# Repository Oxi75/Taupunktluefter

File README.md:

Dies ist meine erweiterte Version vom Taupunktlüfter mit Logging-Funktion der Maker Media GmbH.
Das Original mit den wichtigsten Fragen rund um den Taupunktlüfter beantwortet eine **[FAQ](https://heise.de/-6526328)**. Die vollständigen Artikel zum Projekt gibt es in der **[Make-Ausgabe 1/22 ab Seite 22](https://www.heise.de/select/make/2022/1/2135511212557842576)** und in der **[Make-Ausgabe 2/22 ab Seite 82](https://www.heise.de/select/make/2022/2/2204711461516715363)** zu lesen.

Das Original Github Projekt liegt hier: https://github.com/MakeMagazinDE/Taupunktluefter

# Taupunktlüfter mit Datenlogger V3.1

Sensorspannungsversorgung nicht mehr direkt über +5V sondern über Digital Out 8
des Arduinos angebunden. Hintergrund: Starke Störungen auf den Sensorleitungen,
konnte System in eine Endlos-Reboot-Schleife schicken (permanenter
Sensorfehler). Ende der Schleife erst durch hartes Abschalten der
(Sensor)Spannungsversorgung.

# Taupunktlüfter mit Datenlogger V3.0

* Unterstützung von bis zu vier Tür-Sensoren. D.h. wenn der entsprechende Sensor
anzeigt, dass die Tür nicht geschlossen ist, springt auch der Lüfter nicht an.
Als Sensoren können einfache Schließer (z.B. Magnetschalter) zum Einsatz kommen.
Schalter geschlossen, bedeutet Tür geschlossen.
Auf dem PCB sind Jumper vorgesehen um die Schalter zu überbrücken.
Wird eine offene Tür erkannt, so geht einerseits die Hinweis-LED permanent an,
andererseits wird eine entsprechende Information auf dem Display ausgegeben.
* Display-Auto-Off
Das Backlight des Displays wird nach einer bestimmten Zeit deaktiviert. Um es wieder zu
aktivieren, ist ein dafür vorgesehener Taster zu drücken.
* Umbenennung der Sensoren
„Sensor 1“ und „Sensor 2“ wurden umbenannt nach „Sensor I“ für „Sensor innen“ und
„Sensor A“ für „Sensor außen“.
* Erstellung von Schaltplan und Layout in KiCad 6.0;
Platine passend für Gehäuse Maße: 200 x 120 x 57 mm Deckel klar
https://www.ebay.de/itm/312566082994?var=611287841843

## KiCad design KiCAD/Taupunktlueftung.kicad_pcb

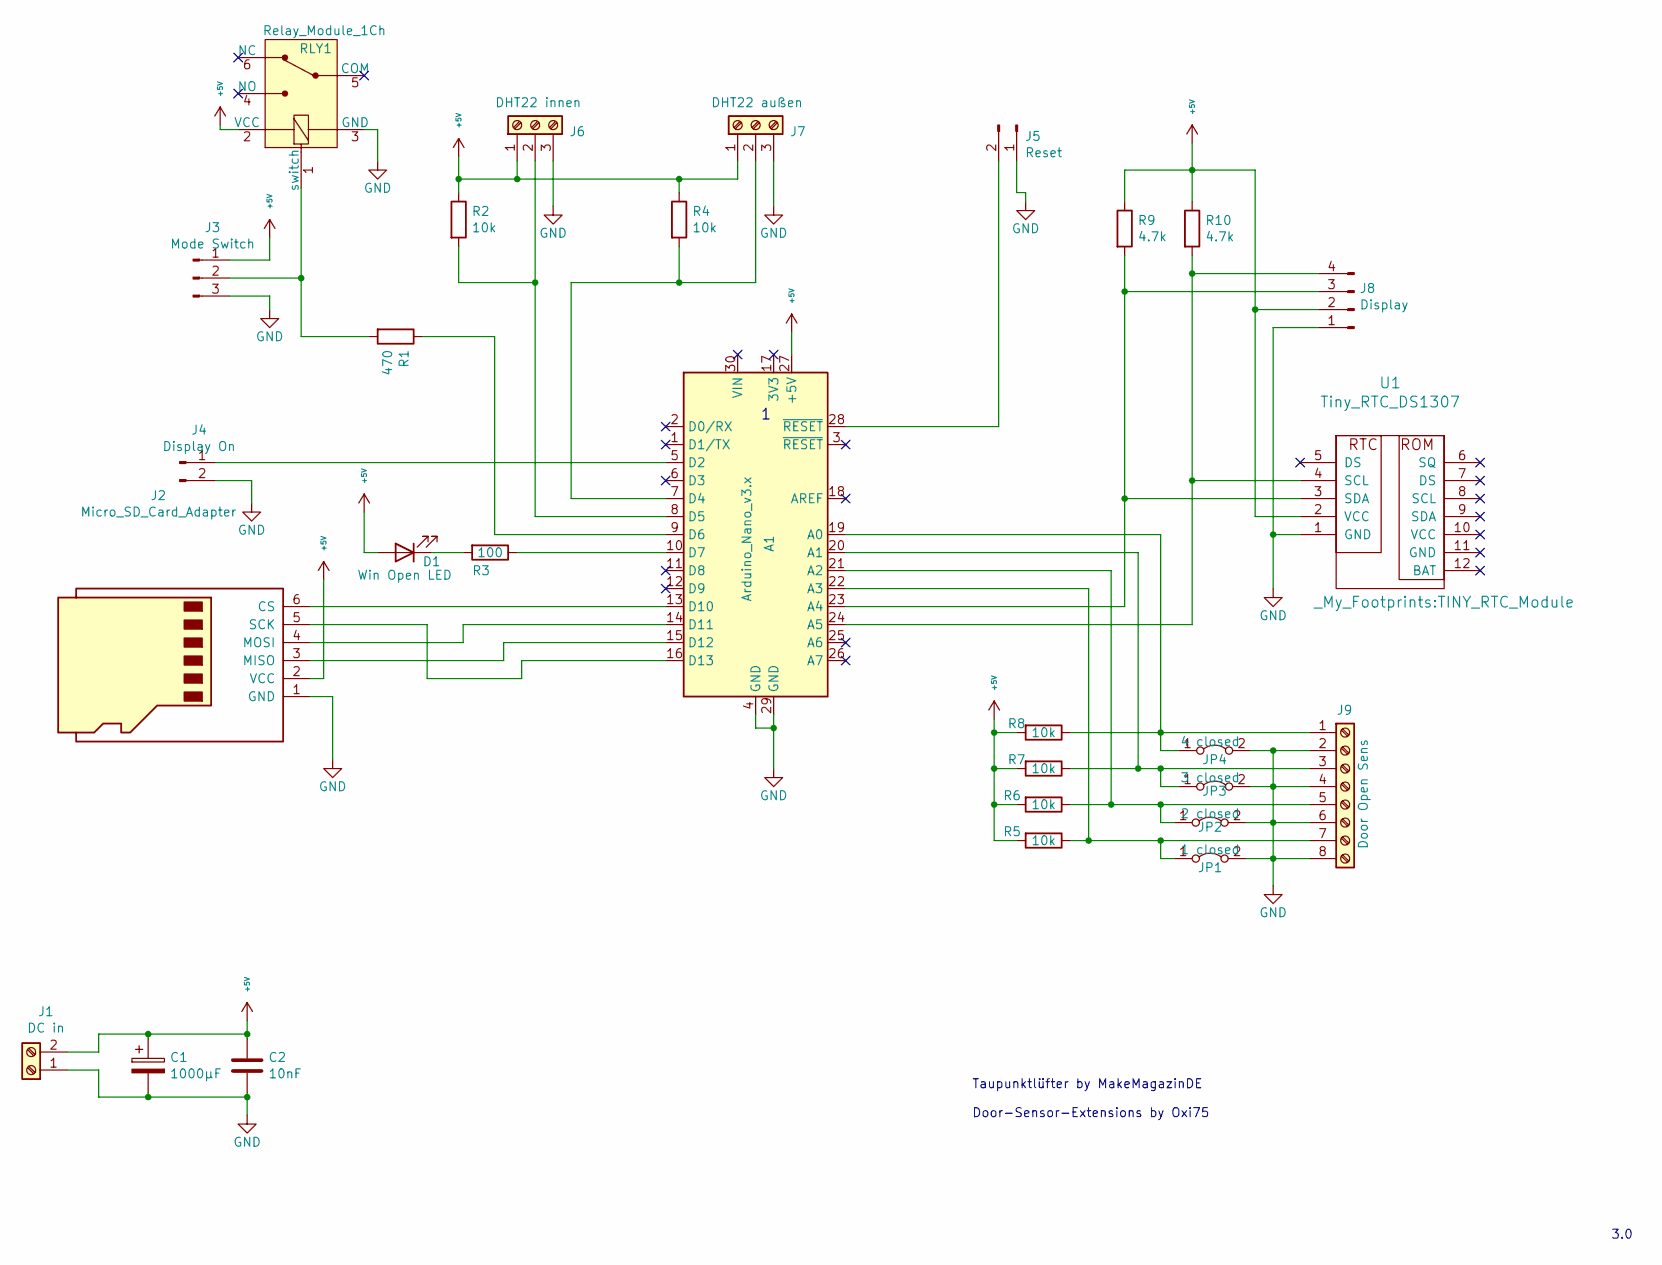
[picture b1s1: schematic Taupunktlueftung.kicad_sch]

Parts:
A1: Arduino_Nano_v3.x; Arduino_Nano
C1: 1000µF; CP_Radial_D8.0mm_P5.00mm
C2: 10nF; C_Rect_L9.0mm_W2.5mm_P7.50mm_MKT
D1: Win Open LED; LED_D5.0mm
J1: DC in; TerminalBlock_RND_205-00012_1x02_P5.00mm_Horizontal
J2: Micro_SD_Card_Adapter; MicroSD-Module_upright
J3: Mode Switch; PinHeader_1x03_P2.54mm_Vertical
J4: Display On; PinHeader_1x02_P2.54mm_Vertical
J5: Reset; PinHeader_1x02_P2.54mm_Vertical
J6: DHT22 innen; TerminalBlock_RND_205-00013_1x03_P5.00mm_Horizontal
J7: DHT22 außen; TerminalBlock_RND_205-00013_1x03_P5.00mm_Horizontal
J8: Display; PinHeader_1x04_P2.54mm_Vertical
J9: Door Open Sens; TerminalBlock_RND_205-00018_1x08_P5.00mm_Horizontal
JP1: 1 closed; PinHeader_1x02_P2.54mm_Vertical
JP2: 2 closed; PinHeader_1x02_P2.54mm_Vertical
JP3: 3 closed; PinHeader_1x02_P2.54mm_Vertical
JP4: 4 closed; PinHeader_1x02_P2.54mm_Vertical
R1: 470; R_Axial_DIN0309_L9.0mm_D3.2mm_P12.70mm_Horizontal
R2, R4, R5, R6, R7, R8: 10k; R_Axial_DIN0309_L9.0mm_D3.2mm_P12.70mm_Horizontal
R3: 100; R_Axial_DIN0309_L9.0mm_D3.2mm_P12.70mm_Horizontal
R9, R10: 4.7k; R_Axial_DIN0309_L9.0mm_D3.2mm_P12.70mm_Horizontal
RLY1: Relay_Module_1Ch
U1: Tiny_RTC_DS1307; TINY_RTC_Module

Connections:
+5V: A1.27 (+5V), C1.1, C2.1, D1.2 (A), J1.2, J2.2 (VCC), J3.1, J6.1, J7.1, J8.2, R2.1, R4.1, R5.2, R6.2, R7.2, R8.2, R9.1, R10.1, RLY1.2 (VCC), U1.2 (VCC)
GND: A1.4 (GND), A1.29 (GND), C1.2, C2.2, J1.1, J2.1 (GND), J3.3, J4.2, J5.1, J6.3, J7.3, J8.1, J9.2, J9.4, J9.6, J9.8, JP1.2 (B), JP2.2 (B), JP3.2 (B), JP4.2 (B), RLY1.3 (GND), U1.1 (GND)
unnamed: A1.5 (D2), J4.1
unnamed: A1.7 (D4), J7.2, R4.2
unnamed: A1.8 (D5), J6.2, R2.2
unnamed: A1.9 (D6), R1.1
unnamed: A1.10 (D7), R3.1
unnamed: A1.13 (D10), J2.6 (CS)
unnamed: A1.14 (D11), J2.4 (MOSI)
unnamed: A1.15 (D12), J2.3 (MISO)
unnamed: A1.16 (D13), J2.5 (SCK)
unnamed: A1.19 (A0), J9.1, JP4.1 (A), R8.1
unnamed: A1.20 (A1), J9.3, JP3.1 (A), R7.1
unnamed: A1.21 (A2), J9.5, JP2.1 (A), R6.1
unnamed: A1.22 (A3), J9.7, JP1.1 (A), R5.1
unnamed: A1.23 (A4), J8.3, R9.2, U1.3 (SDA)
unnamed: A1.24 (A5), J8.4, R10.2, U1.4 (SCL)
unnamed: A1.28 (~RESET), J5.2
unnamed: D1.1 (K), R3.2
unnamed: J3.2, R1.2, RLY1.1 (switch)

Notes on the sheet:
3.0
Taupunktlüfter by MakeMagazinDE Door-Sensor-Extensions by Oxi75

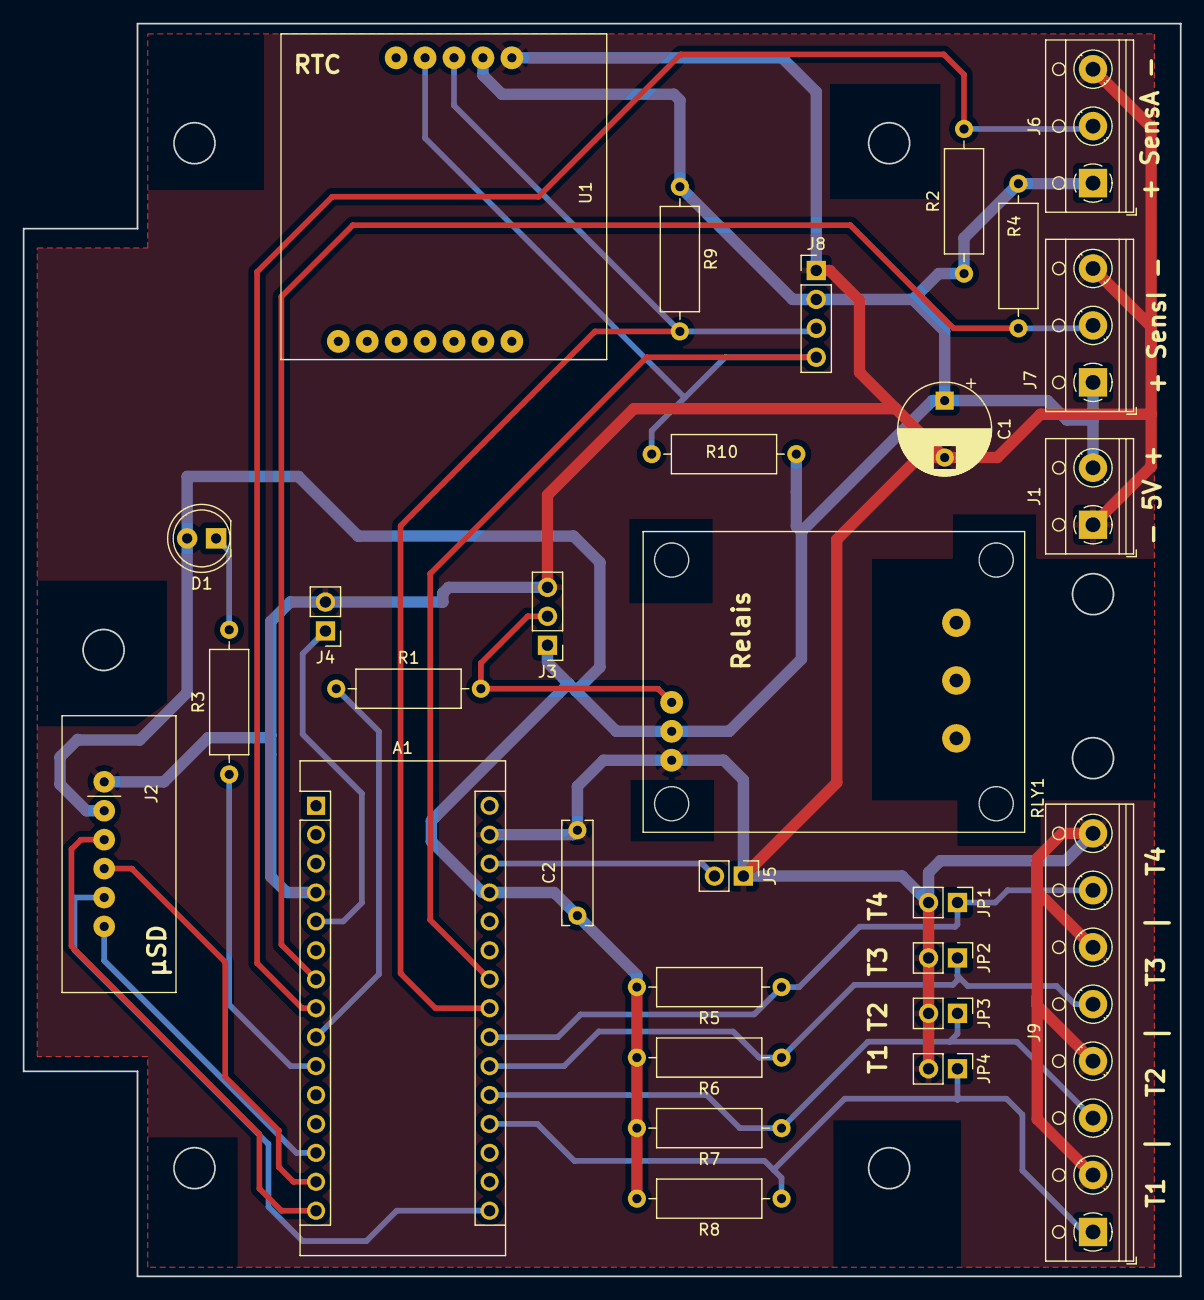
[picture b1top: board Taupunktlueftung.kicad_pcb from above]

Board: 2 copper layers, 101.6 x 110.0 mm, 29 parts (0 on the bottom side), 20 nets.

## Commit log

2022-11-16 removed all old / unwanted files and renamed some files and folders
2022-11-16 renamed ino-file to a common name without version number (better for version management with git)
2022-11-16 renamed again
2022-11-16 Added KiCAD and Gerber Files Modification / Extension of original source code to support door sensors and display auto-off
2022-11-16 Added KiCAD and Gerber Files
2022-11-16 Extension of original source code to support door sensors and display auto-off
2022-11-16 Added functionality to reset (power off/on) sensors on startup; Updated Schmatics
2022-11-16 Updated documentation
2022-11-17 reset correction values to 0
2022-11-17 added Info for V3.1
2022-12-11 Added feedback line from Relais-Input to D9 of Arduino. So it's possible to read back the current van state even if the arduino output signal is overridden by the mode switch.
2023-03-18 Variablen und Header umbenannt. Fix im Datenlogging (hoffentlich). Schaltgrenze auf 3°C abgesenkt (zuvor 5°C)
